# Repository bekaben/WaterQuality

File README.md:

# Precise Irrigation and Smart Water Resources Management

<p align="justify">
Water Quality Monitoring Solution Based on Single Pair Ethernet (SPE), the goal aims to monitor Water quality, Soil moisture, and  assume crop irrigation.

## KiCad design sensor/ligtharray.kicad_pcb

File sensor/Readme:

Proposed sensor for water quality
Design done in Kicad

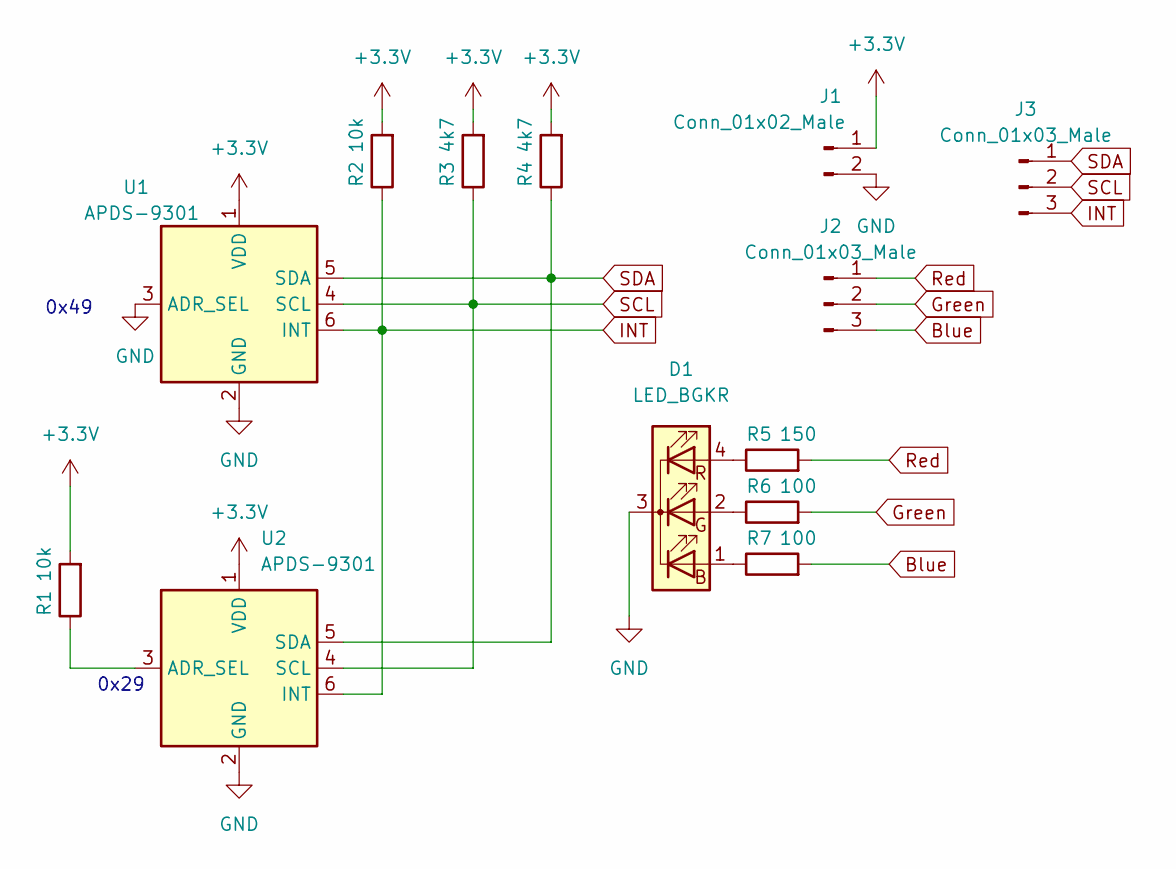
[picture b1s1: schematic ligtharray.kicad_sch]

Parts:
D1: LED_BGKR; LED_SK6812_PLCC4_5.0x5.0mm_P3.2mm
J1: Conn_01x02_Male; PinHeader_1x02_P1.00mm_Horizontal
J2, J3: Conn_01x03_Male; PinHeader_1x03_P1.00mm_Horizontal
R1, R2: 10k; R_0603_1608Metric
R3, R4: 4k7; R_0603_1608Metric
R5: 150; R_0603_1608Metric
R6, R7: 100; R_0603_1608Metric
U1, U2: APDS-9301; Osram_SFH9x0x

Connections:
+3V3: J1.1, R1.2, R2.2, R3.2, R4.2, U1.1 (VDD), U2.1 (VDD)
Blue: J2.3, R7.2
GND: D1.3 (K), J1.2, U1.2 (GND), U1.3 (ADR_SEL), U2.2 (GND)
Green: J2.2, R6.2
INT: J3.3, R2.1, U1.6 (INT), U2.6 (INT)
unnamed: D1.1 (BA), R7.1
unnamed: D1.2 (GA), R6.1
unnamed: D1.4 (RA), R5.1
unnamed: R1.1, U2.3 (ADR_SEL)
Red: J2.1, R5.2
SCL: J3.2, R3.1, U1.4 (SCL), U2.4 (SCL)
SDA: J3.1, R4.1, U1.5 (SDA), U2.5 (SDA)

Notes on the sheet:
0x29
0x49

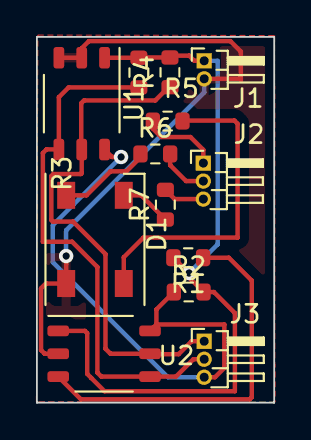
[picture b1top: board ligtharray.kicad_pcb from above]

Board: 2 copper layers, 13.2 x 20.3 mm, 13 parts (0 on the bottom side), 12 nets.

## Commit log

2022-04-21 FPGA_Source
2023-08-29 Rename FPGA to WaterQualityNode
2023-08-29 Rename Readme to Readme.md
